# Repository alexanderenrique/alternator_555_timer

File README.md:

# Alternator 555 Timer

A small analog delay board for classic cars with upgraded alternators. A CMOS 555 monostable holds the alternator field (I wire) off for ~10 seconds after key-on so V-belts can spin up before the load hits — no MCU, no firmware.

**Project page:** [denton.works/projects/alternator-555-timer](https://denton.works/projects/alternator-555-timer/)

## What's here

- KiCad schematic and PCB (`555_I_delay.kicad_*`)
- `BOM.csv` — bill of materials
- `555_v1.zip` — zipped gerbers and drill files for your PCB manufacturer

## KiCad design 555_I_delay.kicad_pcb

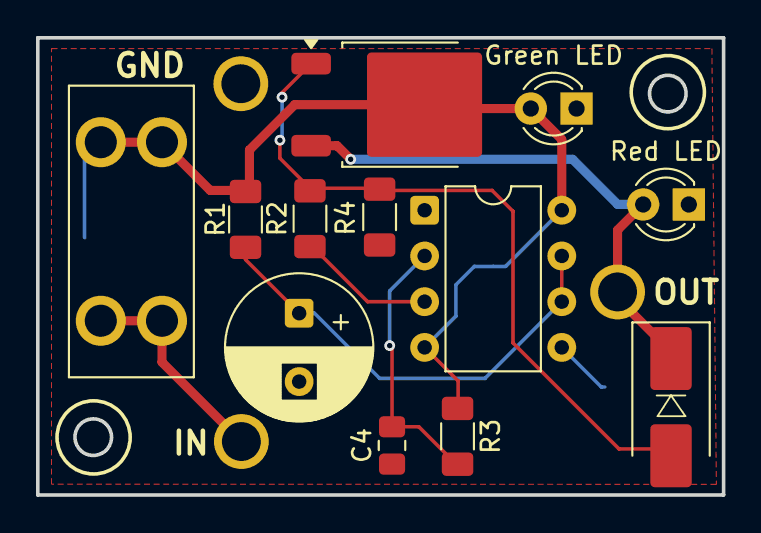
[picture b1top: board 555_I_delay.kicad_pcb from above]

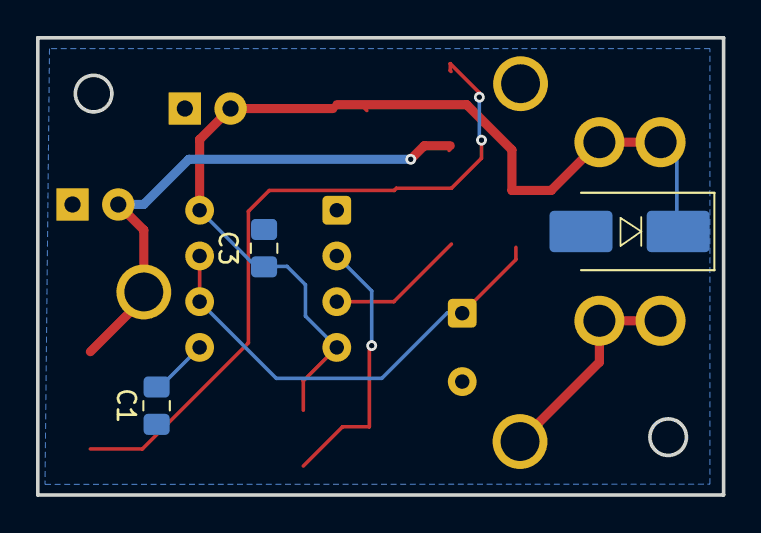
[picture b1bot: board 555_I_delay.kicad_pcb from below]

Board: 2 copper layers, 38.1 x 25.4 mm, 18 parts (3 on the bottom side), 9 nets.

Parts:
C1, C3, C4: 0.1uF; C_0805_2012Metric_Pad1.18x1.45mm_HandSolder
C2: 47uF; CP_Radial_D8.0mm_P3.80mm
D1: TVS; D_SMB_Handsoldering
D2: BZV55B15; D_SMB_Handsoldering
D3: Green LED; LED_D3.0mm_Clear
D4: Red LED; LED_D3.0mm_Clear
F1: Fuse_Small; Fuseholder_Blade_Mini_Keystone_3568
J1: I_In; PinHeader_1x01_P1.00mm_Vertical
J2: I_out; 12_AWG_TH_Alex
J3: GND_Conn; 12_AWG_TH_Alex
Q1: FQD11P06TM; TO-252-2
R1: 220k; R_1206_3216Metric_Pad1.30x1.75mm_HandSolder
R2: 100; R_1206_3216Metric_Pad1.30x1.75mm_HandSolder
R3: 10k; R_1206_3216Metric_Pad1.30x1.75mm_HandSolder
R4: 100k (pulldown); R_1206_3216Metric_Pad1.30x1.75mm_HandSolder
U1: NE555P; DIP-8_W7.62mm

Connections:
GND: C1.1, C2.2, C3.1, C4.1, D2.2 (A), D3.1 (K), D4.1 (K), J3.1 (Pin_1_1), R4.2, U1.1 (GND)
unnamed: D1.2 (A), Q1.1 (G), R2.2, R4.1
unnamed: D1.1 (K), D4.2 (A), J2.1 (Pin_1_1), Q1.3 (S)
unnamed: C3.2, D2.1 (K), D3.2 (A), F1.2, Q1.2 (D), R1.1, R3.1, U1.4 (~RST), U1.8 (VCC)
unnamed: F1.1, J1.1 (Pin_1_1)
unnamed: C1.2, U1.5 (CONT)
unnamed: C2.1, R1.2, U1.6 (THRES), U1.7 (DISCH)
unnamed: R2.1, U1.3 (OUT)
unnamed: C4.2, R3.2, U1.2 (TRIG)

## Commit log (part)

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2026-06-12 added BOM
2026-06-12 cleaned up
